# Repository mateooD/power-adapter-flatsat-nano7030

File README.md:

# Power Adapter – FlatSat Nano 70/30 ⚡🛰️

Placa de distribución y protección de alimentación para el entorno **FlatSat híbrido**, desarrollada en el **Instituto Gulich** en colaboración con el proyecto **CubeSat Nano 70/30** de la **FCEFyN – Universidad Nacional de Córdoba**, en el marco de las **Prácticas Profesionales Supervisadas (PPS)**.

El diseño está orientado a alimentar y validar los subsistemas de **COMMS** y **OBC** durante tareas de integración y ensayo.

---

## 📘 Descripción general

Este repositorio documenta el diseño del **Power Adapter**, una placa de alimentación desarrollada para su uso en el entorno FlatSat híbrido del proyecto CubeSat Nano 70/30.

La placa actúa como interfaz entre la fuente de laboratorio y los subsistemas del satélite, permitiendo una distribución segura de potencia, la incorporación de protecciones eléctricas y la instrumentación necesaria para tareas de prueba, validación e integración del sistema.

---

## 🎯 Objetivos del proyecto

- Diseñar una placa de **distribución de alimentación robusta y segura**.
- Proveer las tensiones requeridas por los subsistemas de **COMMS** y **OBC**.
- Incorporar **protecciones eléctricas** adecuadas para entorno de laboratorio.
- Facilitar la **medición de tensiones y corrientes** durante ensayos.
- Integrar el módulo al flujo de trabajo del **FlatSat híbrido**.
- Documentar el diseño de forma clara y reproducible.

---

## ⚙️ Características principales

- Distribución de múltiples rieles de alimentación.
- Separación entre alimentación lógica y potencia del transmisor.
- Protección mediante fusibles y supresión de transitorios.
- Puntos de test para mediciones eléctricas.
- Diseño implementado íntegramente en **KiCad**.

---

## 🛰️ Subsistemas involucrados

- **COMMS**: NanoCom U482C (Transceptor UHF)
- **OBC**: NanoMind A712C (On-Board Computer)
- **Ground Segment**: TNC1 y estación terrestre de pruebas
- **Entorno de control**: MOC virtual

---
## 📂 Estructura del repositorio

```
power-adapter-flatsat-nano7030/
├── hardware/ # Diseño KiCad del PCB
├── docs/ # Documentación y referencias técnicas
├── images/ # Imágenes y diagramas del proyecto
├── test/ # Resultados de pruebas y validaciones (futuro)
└── README.md
```
---

Cada carpeta incluye su propio README con información específica.

---

## 🛠️ Herramientas utilizadas

- **KiCad** (esquemático y PCB)
- Instrumentación electrónica de laboratorio
- Git y GitHub para control de versiones

---

## 📄 Licencia

Este proyecto se distribuye bajo licencia **MIT**.  
La documentación de terceros incluida como referencia conserva su licencia original.

---

## 📬 Notas finales

El repositorio se publica con fines de documentación técnica y aprendizaje.  
El diseño puede evolucionar a medida que se incorporen nuevas pruebas o revisiones del sistema.
Se agradecen los comentarios y contribuciones constructivas.

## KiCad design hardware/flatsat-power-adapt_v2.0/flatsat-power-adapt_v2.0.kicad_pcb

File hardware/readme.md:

# Proyecto KiCad – Power Adapter FlatSat

Esta carpeta contiene el **diseño completo en KiCad** de la placa *Power Adapter* utilizada en el entorno **FlatSat híbrido** del proyecto **Nano 70/30**.

El proyecto incluye el esquemático y el diseño de PCB correspondientes a la versión **v2.0** del Power Adapter.

---

## 📂 Contenido

- `flatsat-power-adapt_v2.0.kicad_pro`  
  Archivo principal del proyecto KiCad.

- `flatsat-power-adapt_v2.0.kicad_sch`  
  Esquemático eléctrico del Power Adapter.

- `flatsat-power-adapt_v2.0.kicad_pcb`  
  Diseño del PCB.

- `Library.pretty/`  
  Footprints personalizados utilizados en el diseño.

- `fp-lib-table`  
  Tabla de librerías de footprints asociadas al proyecto.

- `fp-info-cache`  
  Archivo de caché generado por KiCad (no esencial para el diseño).

- `*_Edge_Cuts.gbr`, `*_F_Cu.gbr`, `*.drl`, `*.gbrjob`  
  Archivos de fabricación (Gerbers y taladros) generados desde KiCad.

- `*-backups/`  
  Copias de respaldo automáticas generadas por KiCad.

---

## ℹ️ Notas

- Los archivos de respaldo y caché se mantienen para referencia histórica, pero no son necesarios para reproducir el diseño.
- El proyecto fue desarrollado y editado utilizando **KiCad**.
- Para fabricar la placa, se recomienda utilizar los archivos Gerber y de taladrado incluidos o regenerarlos desde el proyecto.

---

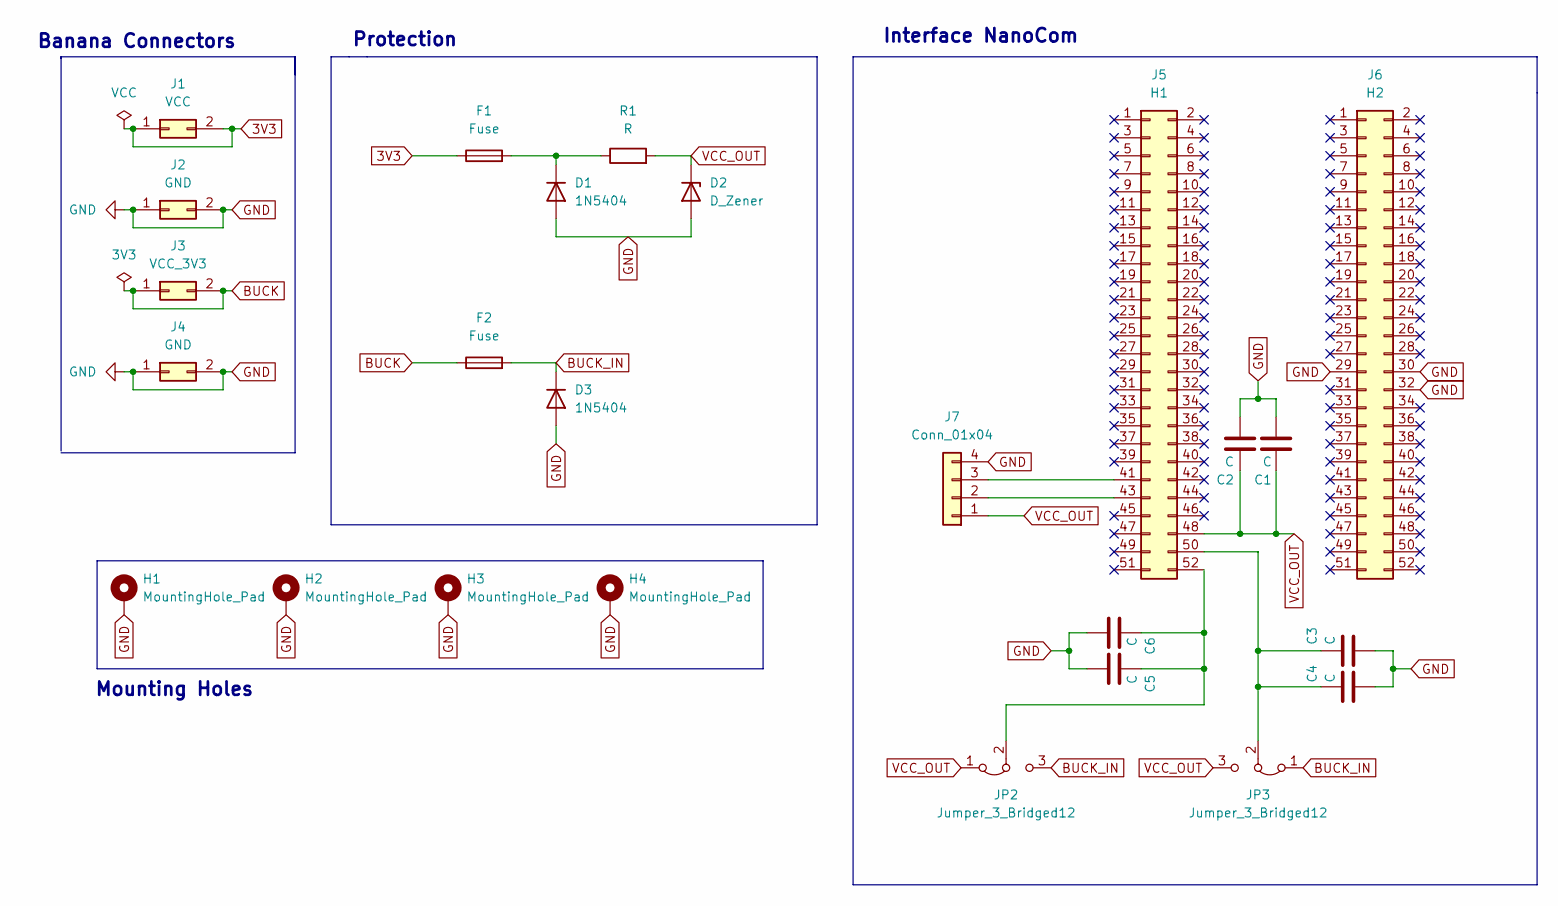
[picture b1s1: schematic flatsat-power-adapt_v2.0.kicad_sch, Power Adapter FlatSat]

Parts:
C1, C2, C3, C4, C5, C6: C; C_0805_2012Metric_Pad1.18x1.45mm_HandSolder
D1, D3: 1N5404; D_DO-41_SOD81_P10.16mm_Horizontal
D2: D_Zener; D_DO-41_SOD81_P10.16mm_Horizontal
F1, F2: Fuse; D_DO-41_SOD81_P10.16mm_Horizontal
H1, H2, H3, H4: MountingHole_Pad; MountingHole_3mm_nanocom
J1: VCC; Banana_Jack_2Pin_v_cubesat
J2, J4: GND; Banana_Jack_2Pin_v_cubesat
J3: VCC_3V3; Banana_Jack_2Pin_v_cubesat
J5: H1; PinSocket_2x26_P2.54mm_Vertical_MIRROR_v2
J6: H2; PinSocket_2x26_P2.54mm_Vertical_MIRROR_v2
J7: Conn_01x04; PinHeader_1x04_P2.54mm_Horizontal
JP2, JP3: Jumper_3_Bridged12; PinHeader_1x03_P2.54mm_Vertical
R1: R; R_Axial_DIN0309_L9.0mm_D3.2mm_P12.70mm_Horizontal

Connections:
3V3: F1.1, J1.1, J1.2
BUCK: F2.1, J3.1, J3.2
BUCK_IN: D3.1 (K), F2.2, JP2.3 (B), JP3.1 (A)
GND: C1.2, C2.2, C3.2, C4.2, C5.2, C6.2, D1.2 (A), D2.2 (A), D3.2 (A), H1.1, H2.1, H3.1, H4.1, J2.1, J2.2, J4.1, J4.2, J6.29, J6.30, J6.32, J7.4
unnamed: D1.1 (K), F1.2, R1.1
unnamed: J5.41, J7.3
unnamed: J5.43, J7.2
unnamed: C3.1, C4.1, J5.50, JP3.2 (C)
unnamed: C5.1, C6.1, J5.52, JP2.2 (C)
VCC_OUT: C1.1, C2.1, D2.1 (K), J5.48, J7.1, JP2.1 (A), JP3.3 (B), R1.2

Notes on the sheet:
Interface NanoCom
Mounting Holes
Banana Connectors
Protection

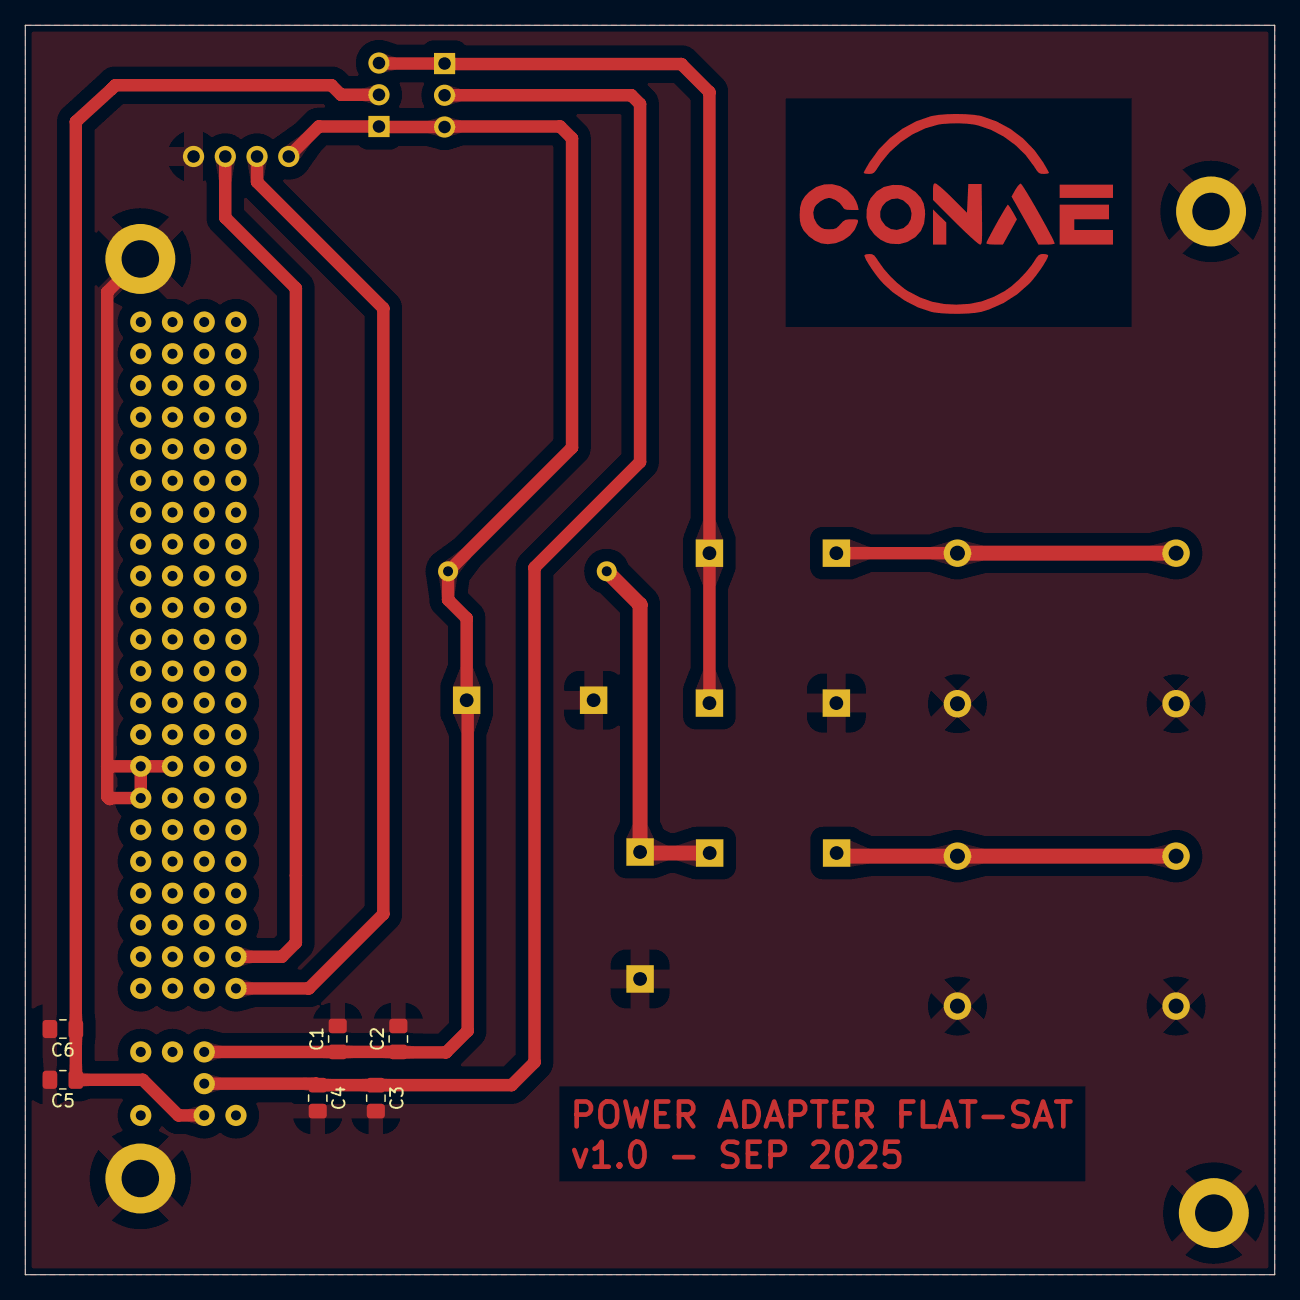
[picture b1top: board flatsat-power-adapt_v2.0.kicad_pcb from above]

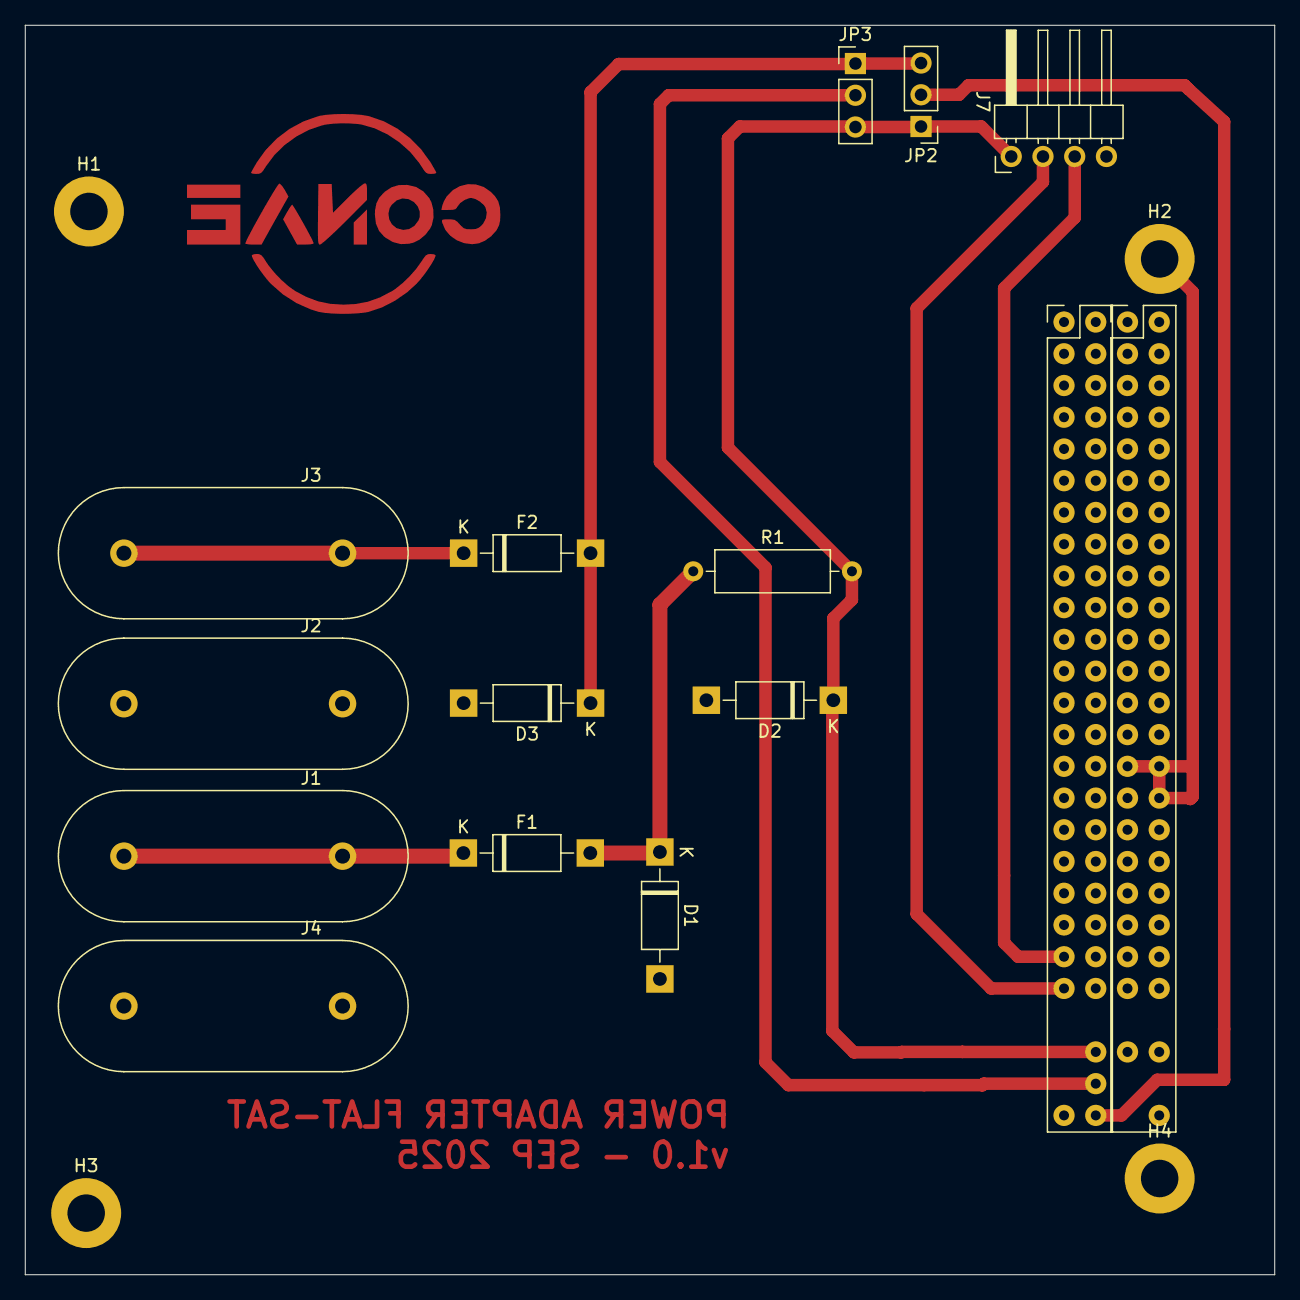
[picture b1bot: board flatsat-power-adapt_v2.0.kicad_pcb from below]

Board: 2 copper layers, 100.0 x 100.0 mm, 25 parts (19 on the bottom side), 10 nets.

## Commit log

2025-12-26 adding files
2025-12-26 readme y archivos utiles
2025-12-29 add pics
2025-12-29 fix pics
2025-12-29 fix struct
2025-12-29 fix structure
2025-12-29 fix structure repo
2025-12-29 fix structure repository
